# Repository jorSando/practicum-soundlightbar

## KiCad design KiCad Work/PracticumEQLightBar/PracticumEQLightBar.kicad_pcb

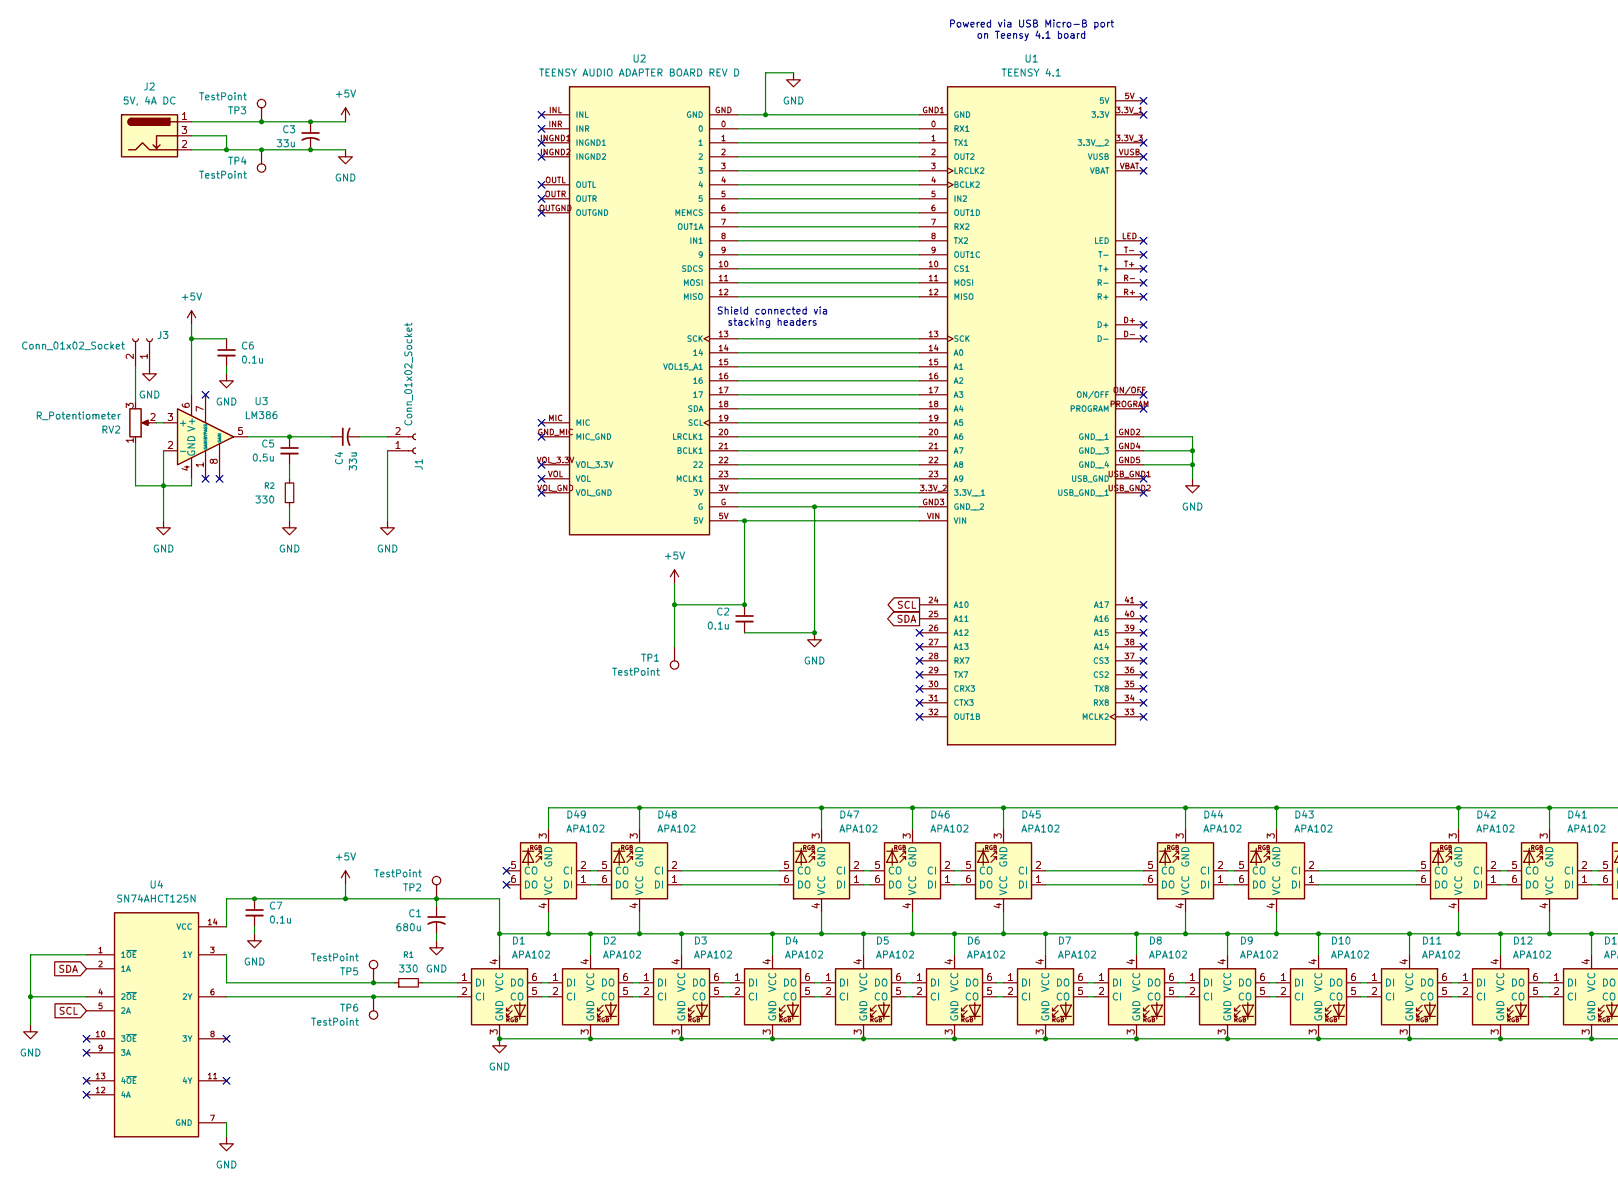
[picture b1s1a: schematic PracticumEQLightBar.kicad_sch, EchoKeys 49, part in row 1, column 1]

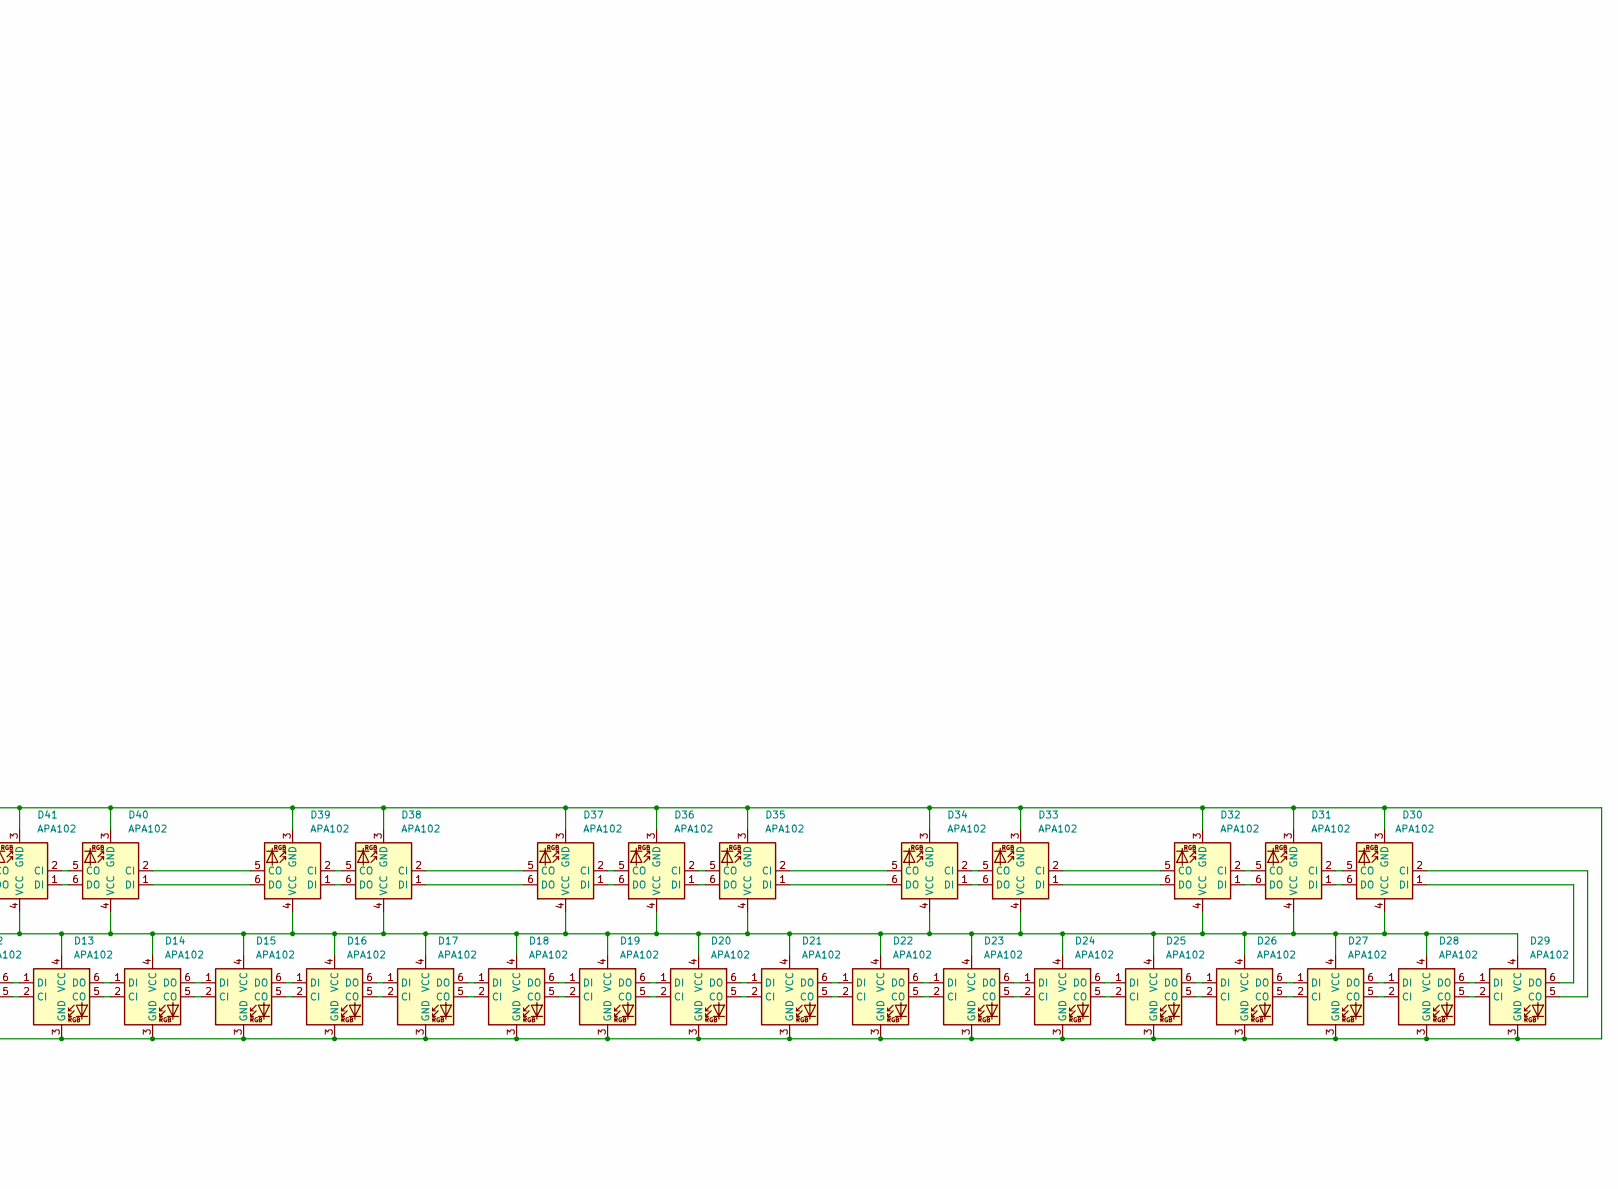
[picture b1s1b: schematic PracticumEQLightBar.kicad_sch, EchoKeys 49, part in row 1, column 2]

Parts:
C1: 680u; CP_Radial_D8.0mm_P3.80mm
C2, C6, C7: 0.1u; C_Disc_D4.7mm_W2.5mm_P5.00mm
C3, C4: 33u; CP_Radial_D4.0mm_P2.00mm
C5: 0.5u; C_Disc_D4.7mm_W2.5mm_P5.00mm
D1, D2, D3, D4, D5, D6, D7, D8, D9, D10, D11, D12, D13, D14, D15, D16, D17, D18, D19, D20, D21, D22, D23, D24, D25, D26, D27, D28, D29, D30, D31, D32, D33, D34, D35, D36, D37, D38, D39, D40, D41, D42, D43, D44, D45, D46, D47, D48, D49: APA102; LED_RGB_5050-6
J1, J3: Conn_01x02_Socket; PinHeader_1x02_P2.54mm_Vertical
J2: 5V, 4A DC; 694106301002_1
R1, R2: 330; R_Axial_DIN0207_L6.3mm_D2.5mm_P7.62mm_Horizontal
RV2: R_Potentiometer; PTV09A4030FA104 Pot 100k
TP1, TP2, TP3, TP4: TestPoint; TestPoint_Pad_1.0x1.0mm
TP5, TP6: TestPoint; PinHeader_1x01_P2.54mm_Vertical
U1: TEENSY 4.1; Double PinSocket_1x24_P2.54mm_Vertical (Teensy 4_1); PARTREV 4.1
U2: TEENSY AUDIO ADAPTER BOARD REV D; MODULE_DEV-15845
U3: LM386; DIP-8_W7.62mm
U4: SN74AHCT125N; DIP794W45P254L1930H508Q14; PARTREV Q

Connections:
+5V: C1.1, C2.1, C3.1, C6.1, C7.1, D1.4 (VCC), D2.4 (VCC), D3.4 (VCC), D4.4 (VCC), D5.4 (VCC), D6.4 (VCC), D7.4 (VCC), D8.4 (VCC), D9.4 (VCC), D10.4 (VCC), D11.4 (VCC), D12.4 (VCC), D13.4 (VCC), D14.4 (VCC), D15.4 (VCC), D16.4 (VCC), D17.4 (VCC), D18.4 (VCC), D19.4 (VCC), D20.4 (VCC), D21.4 (VCC), D22.4 (VCC), D23.4 (VCC), D24.4 (VCC), D25.4 (VCC), D26.4 (VCC), D27.4 (VCC), D28.4 (VCC), D29.4 (VCC), D30.4 (VCC), D31.4 (VCC), D32.4 (VCC), D33.4 (VCC), D34.4 (VCC), D35.4 (VCC), D36.4 (VCC), D37.4 (VCC), D38.4 (VCC), D39.4 (VCC), D40.4 (VCC), D41.4 (VCC), D42.4 (VCC), D43.4 (VCC), D44.4 (VCC), D45.4 (VCC), D46.4 (VCC), D47.4 (VCC), D48.4 (VCC), D49.4 (VCC), J2.1, TP1.1, TP2.1, TP3.1, U1.VIN, U2.5V, U3.6 (V+), U4.14 (VCC)
GND: C1.2, C2.2, C3.2, C6.2, C7.2, D1.3 (GND), D2.3 (GND), D3.3 (GND), D4.3 (GND), D5.3 (GND), D6.3 (GND), D7.3 (GND), D8.3 (GND), D9.3 (GND), D10.3 (GND), D11.3 (GND), D12.3 (GND), D13.3 (GND), D14.3 (GND), D15.3 (GND), D16.3 (GND), D17.3 (GND), D18.3 (GND), D19.3 (GND), D20.3 (GND), D21.3 (GND), D22.3 (GND), D23.3 (GND), D24.3 (GND), D25.3 (GND), D26.3 (GND), D27.3 (GND), D28.3 (GND), D29.3 (GND), D30.3 (GND), D31.3 (GND), D32.3 (GND), D33.3 (GND), D34.3 (GND), D35.3 (GND), D36.3 (GND), D37.3 (GND), D38.3 (GND), D39.3 (GND), D40.3 (GND), D41.3 (GND), D42.3 (GND), D43.3 (GND), D44.3 (GND), D45.3 (GND), D46.3 (GND), D47.3 (GND), D48.3 (GND), D49.3 (GND), J1.1, J2.2, J2.3, J3.1, R2.1, RV2.1, TP4.1, U1.GND1 (GND), U1.GND2 (GND__1), U1.GND3 (GND__2), U1.GND4 (GND__3), U1.GND5 (GND__4), U2.G, U2.GND, U3.2 (-), U3.4 (GND), U4.1 (1~OE), U4.4 (2~OE), U4.7 (GND); also elsewhere on the board
unnamed: C4.1, C5.1, U3.5
unnamed: C5.2, R2.2
unnamed: D1.2 (CI), TP6.1, U4.6 (2Y)
unnamed: D1.5 (CO), D2.2 (CI)
unnamed: D1.1 (DI), R1.2
unnamed: D1.6 (DO), D2.1 (DI)
unnamed: D2.5 (CO), D3.2 (CI)
unnamed: D2.6 (DO), D3.1 (DI)
unnamed: D3.5 (CO), D4.2 (CI)
unnamed: D3.6 (DO), D4.1 (DI)
unnamed: D4.5 (CO), D5.2 (CI)
unnamed: D4.6 (DO), D5.1 (DI)
unnamed: D5.5 (CO), D6.2 (CI)
unnamed: D5.6 (DO), D6.1 (DI)
unnamed: D6.5 (CO), D7.2 (CI)
unnamed: D6.6 (DO), D7.1 (DI)
unnamed: D7.5 (CO), D8.2 (CI)
unnamed: D7.6 (DO), D8.1 (DI)
unnamed: D8.5 (CO), D9.2 (CI)
unnamed: D8.6 (DO), D9.1 (DI)
unnamed: D9.5 (CO), D10.2 (CI)
unnamed: D10.5 (CO), D11.2 (CI)
unnamed: D9.6 (DO), D10.1 (DI)
unnamed: D10.6 (DO), D11.1 (DI)
unnamed: D11.5 (CO), D12.2 (CI)
unnamed: D11.6 (DO), D12.1 (DI)
unnamed: D12.5 (CO), D13.2 (CI)
unnamed: D12.6 (DO), D13.1 (DI)
unnamed: D13.5 (CO), D14.2 (CI)
unnamed: D13.6 (DO), D14.1 (DI)
unnamed: D14.5 (CO), D15.2 (CI)
unnamed: D14.6 (DO), D15.1 (DI)
unnamed: D15.5 (CO), D16.2 (CI)
unnamed: D15.6 (DO), D16.1 (DI)
unnamed: D16.5 (CO), D17.2 (CI)
unnamed: D16.6 (DO), D17.1 (DI)
unnamed: D17.5 (CO), D18.2 (CI)
unnamed: D17.6 (DO), D18.1 (DI)
unnamed: D18.5 (CO), D19.2 (CI)
unnamed: D18.6 (DO), D19.1 (DI)
unnamed: D19.5 (CO), D20.2 (CI)
unnamed: D19.6 (DO), D20.1 (DI)
unnamed: D20.5 (CO), D21.2 (CI)
unnamed: D20.6 (DO), D21.1 (DI)
unnamed: D21.5 (CO), D22.2 (CI)
unnamed: D21.6 (DO), D22.1 (DI)
unnamed: D22.5 (CO), D23.2 (CI)
unnamed: D22.6 (DO), D23.1 (DI)
unnamed: D23.5 (CO), D24.2 (CI)
unnamed: D23.6 (DO), D24.1 (DI)
unnamed: D24.5 (CO), D25.2 (CI)
unnamed: D24.6 (DO), D25.1 (DI)
unnamed: D25.5 (CO), D26.2 (CI)
unnamed: D25.6 (DO), D26.1 (DI)
unnamed: D26.5 (CO), D27.2 (CI)
unnamed: D26.6 (DO), D27.1 (DI)
unnamed: D27.5 (CO), D28.2 (CI)
unnamed: D27.6 (DO), D28.1 (DI)
unnamed: D28.5 (CO), D29.2 (CI)
unnamed: D28.6 (DO), D29.1 (DI)
unnamed: D29.5 (CO), D30.2 (CI)
unnamed: D29.6 (DO), D30.1 (DI)
unnamed: D30.5 (CO), D31.2 (CI)
unnamed: D30.6 (DO), D31.1 (DI)
unnamed: D31.5 (CO), D32.2 (CI)
unnamed: D31.6 (DO), D32.1 (DI)
unnamed: D32.5 (CO), D33.2 (CI)
unnamed: D32.6 (DO), D33.1 (DI)
unnamed: D33.5 (CO), D34.2 (CI)
unnamed: D33.6 (DO), D34.1 (DI)
unnamed: D34.5 (CO), D35.2 (CI)
unnamed: D34.6 (DO), D35.1 (DI)
unnamed: D35.5 (CO), D36.2 (CI)
unnamed: D35.6 (DO), D36.1 (DI)
unnamed: D36.5 (CO), D37.2 (CI)
unnamed: D36.6 (DO), D37.1 (DI)
unnamed: D37.5 (CO), D38.2 (CI)
unnamed: D37.6 (DO), D38.1 (DI)
unnamed: D38.5 (CO), D39.2 (CI)
unnamed: D38.6 (DO), D39.1 (DI)
unnamed: D39.5 (CO), D40.2 (CI)
unnamed: D39.6 (DO), D40.1 (DI)
unnamed: D40.5 (CO), D41.2 (CI)
unnamed: D40.6 (DO), D41.1 (DI)
unnamed: D41.5 (CO), D42.2 (CI)
unnamed: D41.6 (DO), D42.1 (DI)
unnamed: D42.5 (CO), D43.2 (CI)
unnamed: D42.6 (DO), D43.1 (DI)
unnamed: D43.5 (CO), D44.2 (CI)
unnamed: D43.6 (DO), D44.1 (DI)
unnamed: D44.5 (CO), D45.2 (CI)
unnamed: D44.6 (DO), D45.1 (DI)
unnamed: D45.5 (CO), D46.2 (CI)
unnamed: D45.6 (DO), D46.1 (DI)
unnamed: D46.5 (CO), D47.2 (CI)
unnamed: D46.6 (DO), D47.1 (DI)
unnamed: D47.5 (CO), D48.2 (CI)
unnamed: D47.6 (DO), D48.1 (DI)
unnamed: D48.5 (CO), D49.2 (CI)
unnamed: D48.6 (DO), D49.1 (DI)
unnamed: C4.2, J1.2
unnamed 103: J3.2, RV2.3; also elsewhere on the board
unnamed: U1.3.3V_2 (3.3V__1), U2.3V
unnamed: U1.14 (A0), U2.14
unnamed: U1.15 (A1), U2.15 (VOL15_A1)
unnamed: U1.16 (A2), U2.16
unnamed: U1.17 (A3), U2.17
unnamed: U1.18 (A4), U2.18 (SDA)
unnamed: U1.19 (A5), U2.19 (SCL)
unnamed: U1.20 (A6), U2.20 (LRCLK1)
unnamed: U1.21 (A7), U2.21 (BCLK1)
unnamed: U1.22 (A8), U2.22
unnamed: U1.23 (A9), U2.23 (MCLK1)
unnamed: U1.4 (BCLK2), U2.4
unnamed: U1.10 (CS1), U2.10 (SDCS)
unnamed: U1.5 (IN2), U2.5
unnamed: U1.3 (LRCLK2), U2.3
unnamed: U1.12 (MISO), U2.12 (MISO)
unnamed: U1.11 (MOSI), U2.11 (MOSI)
unnamed: U1.9 (OUT1C), U2.9
unnamed: U1.6 (OUT1D), U2.6 (MEMCS)
unnamed: U1.2 (OUT2), U2.2
unnamed: U1.0 (RX1), U2.0
unnamed: U1.7 (RX2), U2.7 (OUT1A)
unnamed: U1.13 (SCK), U2.13 (SCK)
unnamed: U1.1 (TX1), U2.1
unnamed: U1.8 (TX2), U2.8 (IN1)
unnamed 129: RV2.2, U3.3 (+); also elsewhere on the board
unnamed: R1.1, TP5.1, U4.3 (1Y)
SCL: U1.24 (A10), U4.5 (2A)
SDA: U1.25 (A11), U4.2 (1A)

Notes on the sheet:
Powered via USB Micro-B port on Teensy 4.1 board
Shield connected via stacking headers

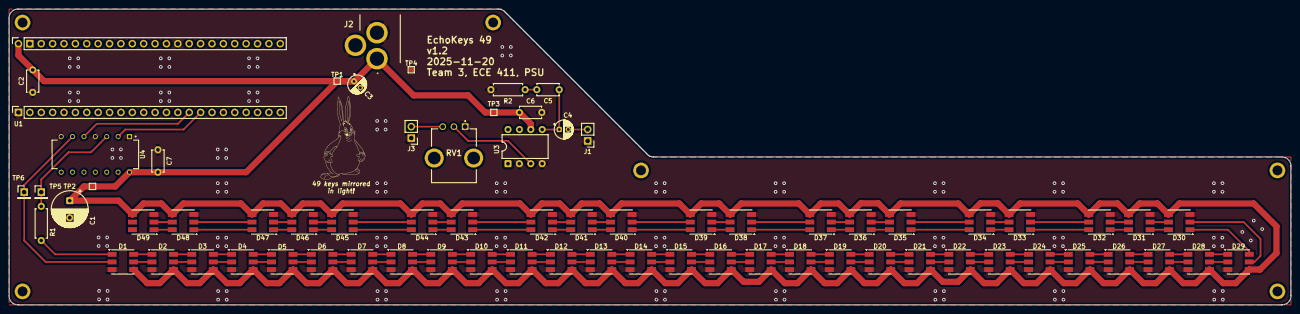
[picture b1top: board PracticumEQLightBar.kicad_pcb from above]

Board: 2 copper layers, 286.0 x 66.0 mm, 71 parts (0 on the bottom side), 108 nets.

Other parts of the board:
RV1: R_Potentiometer; PTV09A4030FA104 Pot 100k

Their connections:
GND: RV1.1; also elsewhere on the board
unnamed 103: RV1.3; also elsewhere on the board
unnamed 129: RV1.2; also elsewhere on the board

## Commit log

2025-10-29 Adding KiCad Project folder
2025-10-29 Added LEDs and wired them in schematic
2025-10-29 Added Git quick guide
2025-10-29 Updates to LED layout to match 49 key on schematic and PCB
2025-10-29 Branched off of Nick to work on preliminary schematic
2025-10-30 Completed preliminary schematic
2025-11-04 prelim for new branch
2025-11-05 Schematic and PCB updated to show all 49 LEDs
2025-11-09 Resized edge cuts and updated titleblocks
2025-11-09 Added PDFs of PCB and Schematic
2025-11-10 Breadboard Prototype
    Soldered prototyping parts and getting an SMD LED working.
2025-11-11 Added SN74 logic level shifter to schematic and PCB
2025-11-13 Updated rev 1.1 drawing sheet PDFs
2025-11-14 Header foot prints added for Teensy. Routing fixes, Reduced board size.
2025-11-14 Commited wrong version last time
2025-11-17 Added unified power, caps, Data in resistor. Modified placements to match enclosure I/O git status
2025-11-18 Initial commit of preliminary code
2025-11-19 Reoriented footprints, larger track width
2025-11-19 DC jack changed to 2.1mm
2025-11-19 Rerouting, smaller board size, keys enclosure sizing
2025-11-20 Added test points
2025-11-20 added horrible power bus for LEDs
2025-11-20 final PCB layout
2025-11-20 Drawing sheets updated with final PCB design
2025-12-03 Replacing FFT with YIN for better pitch detection
2025-12-04 Test plan assignment upload to collaboration site.
2025-12-12 Changed code to make it work with piano notes. Also added LED mapping.
